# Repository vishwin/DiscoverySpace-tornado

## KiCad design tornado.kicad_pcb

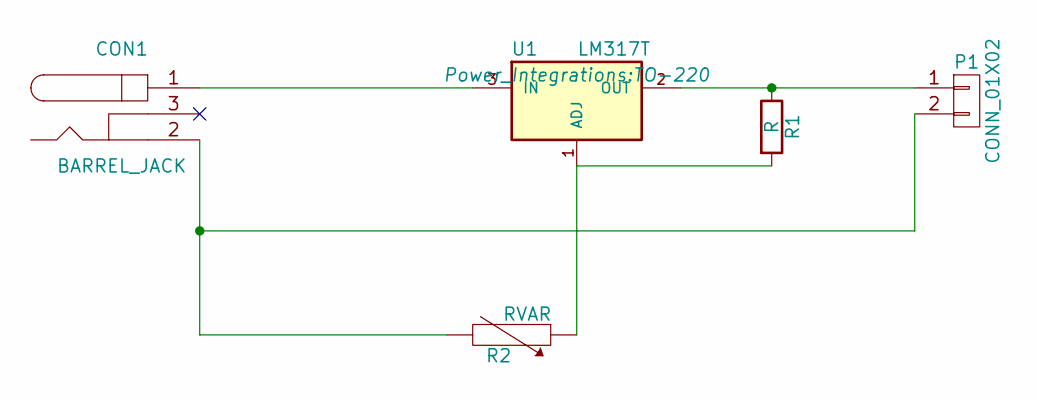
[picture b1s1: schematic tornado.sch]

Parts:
CON1: BARREL_JACK
P1: CONN_01X02; TerminalBlock_Pheonix_MKDS1.5-2pol
R1: R; R_1206
R2: RVAR; TerminalBlock_Pheonix_MKDS1.5-2pol
U1: LM317T; TO-220

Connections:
unnamed: CON1.1, U1.3 (IN)
unnamed: CON1.2, P1.2, R2.2
unnamed: P1.1, R1.1, U1.2 (OUT)
unnamed: R1.2, R2.1, U1.1 (ADJ)

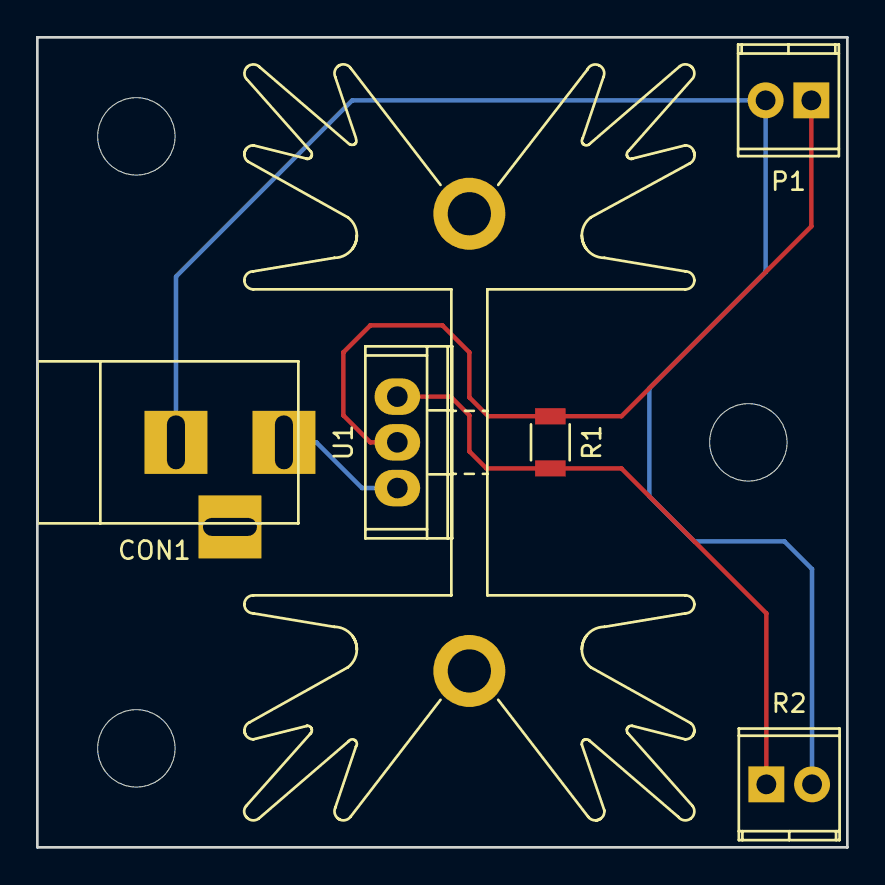
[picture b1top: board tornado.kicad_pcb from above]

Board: 2 copper layers, 45.0 x 45.0 mm, 5 parts (0 on the bottom side), 4 nets.

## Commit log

2016-05-09 Initial commit of already completed design
2016-05-09 Okay fine here's a rendering
